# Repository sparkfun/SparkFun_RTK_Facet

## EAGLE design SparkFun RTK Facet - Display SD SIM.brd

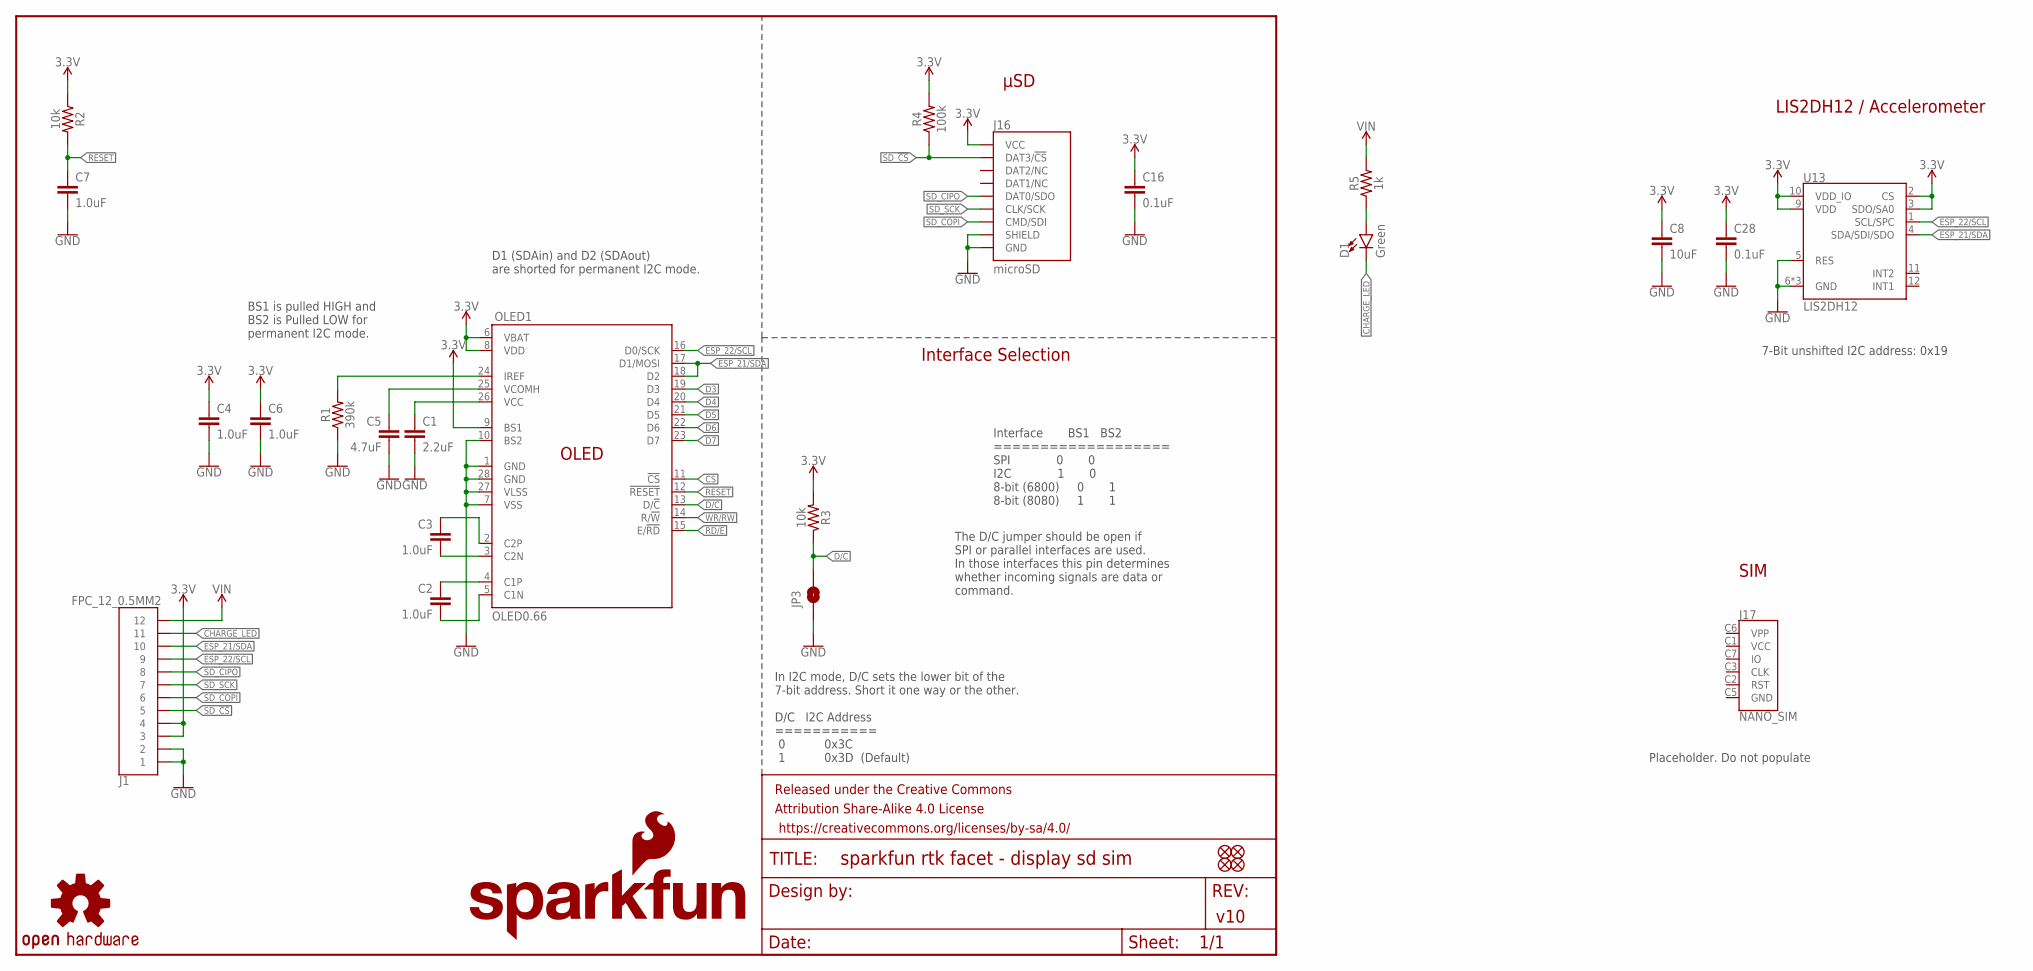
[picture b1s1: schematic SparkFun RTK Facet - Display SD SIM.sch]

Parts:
C1: 2.2uF; 0805
C2, C3: 1.0uF; 0805
C4, C6, C7: 1.0uF; 0603
C5: 4.7uF; 1206
C8: 10uF; 0603
C16, C28: 0.1uF; 0603
D1: Green; LED-1206-BOTTOM
FID1, FID2, FID3, FID4: FIDUCIAL1X2; FIDUCIAL-1X2
FRAME1: FRAME-LETTER; CREATIVE_COMMONS
J1: FPC_12_0.5MM2; FPC_12_FLIP_DOUBLESIDED_2
J16: microSD; MICRO-SD-SOCKET
J17: NANO_SIM; NANO_SIM_WURTH_693043020611
JP3: JUMPER-SMT_2_NO_SILK; SMT-JUMPER_2_NO_SILK
LOGO3: OSHW-LOGOS; OSHW-LOGO-S
LOGO5: SFE_LOGO_NAME_FLAME.1_INCH; SFE_LOGO_NAME_FLAME_.1
OLED1: OLED0.66; OLED-0.66-64X48
R1: 390k; 0603
R2, R3: 10k; 0603
R4: 100k; 0603
R5: 1k; 0603
U13: LIS2DH12; LGA-12-LISDH12

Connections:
3.3V: C4.1, C6.1, C8.1, C16.1, C28.1, J1.3, J1.4, J16.VCC, OLED1.6 (VBAT), OLED1.8 (VDD), OLED1.9 (BS1), R2.1, R3.2, R4.2, U13.2 (CS), U13.3 (SDO/SA0), U13.9 (VDD), U13.10 (VDD_IO)
C1P: C2.1, OLED1.4 (C1P)
C2N: C3.2, OLED1.3 (C2N)
CHARGE_LED: D1.C, J1.11
CS: OLED1.11 (!CS!)
D3: OLED1.19 (D3)
D4: OLED1.20 (D4)
D5: OLED1.21 (D5)
D6: OLED1.22 (D6)
D7: OLED1.23 (D7)
D/C: JP3.2, OLED1.13 (D/!C!), R3.1
ESP_21/SDA: J1.10, OLED1.17 (D1/MOSI), OLED1.18 (D2), U13.4 (SDA/SDI/SDO)
ESP_22/SCL: J1.9, OLED1.16 (D0/SCK), U13.1 (SCL/SPC)
GND: C1.2, C4.2, C5.2, C6.2, C7.2, C8.2, C16.2, C28.2, J1.1, J1.2, J16.CD1 (SHIELD), J16.GND, J16.GND1 (GND), J16.GND3 (GND), JP3.1, OLED1.1 (GND), OLED1.7 (VSS), OLED1.10 (BS2), OLED1.27 (VLSS), OLED1.28 (GND), R1.1, U13.5 (RES), U13.6 (GND), U13.7 (GND), U13.8 (GND)
IREF: OLED1.24 (IREF), R1.2
unnamed: C3.1, OLED1.2 (C2P)
unnamed: C2.2, OLED1.5 (C1N)
unnamed: D1.A, R5.1
RD/E: OLED1.15 (E/!RD!)
RESET: C7.1, OLED1.12 (!RESET!), R2.2
SD_!CS!: J1.5, J16.CS/DAT3 (DAT3/!CS!), R4.1
SD_CIPO: J1.8, J16.DO/DAT0 (DAT0/SDO)
SD_COPI: J1.6, J16.DI/CMD (CMD/SDI)
SD_SCK: J1.7, J16.SCLK (CLK/SCK)
VCC: C1.1, OLED1.26 (VCC)
VCOMH: C5.1, OLED1.25 (VCOMH)
VIN: J1.12, R5.2
WR/RW: OLED1.14 (R/!W!)

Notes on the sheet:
v10
Interface BS1 BS2 =================== SPI 0 0 I2C 1 0 8-bit (6800) 0 1 8-bit (8080) 1 1
Interface Selection
D1 (SDAin) and D2 (SDAout) are shorted for permanent I2C mode.
In I2C mode, D/C sets the lower bit of the 7-bit address. Short it one way or the other. D/C I2C Address =========== 0 0x3C 1 0x3D (Default)
The D/C jumper should be open if SPI or parallel interfaces are used. In those interfaces this pin determines whether incoming signals are data or command.
BS1 is pulled HIGH and BS2 is Pulled LOW for permanent I2C mode.
μSD
7-Bit unshifted I2C address: 0x19
LIS2DH12 / Accelerometer
SIM
Placeholder. Do not populate

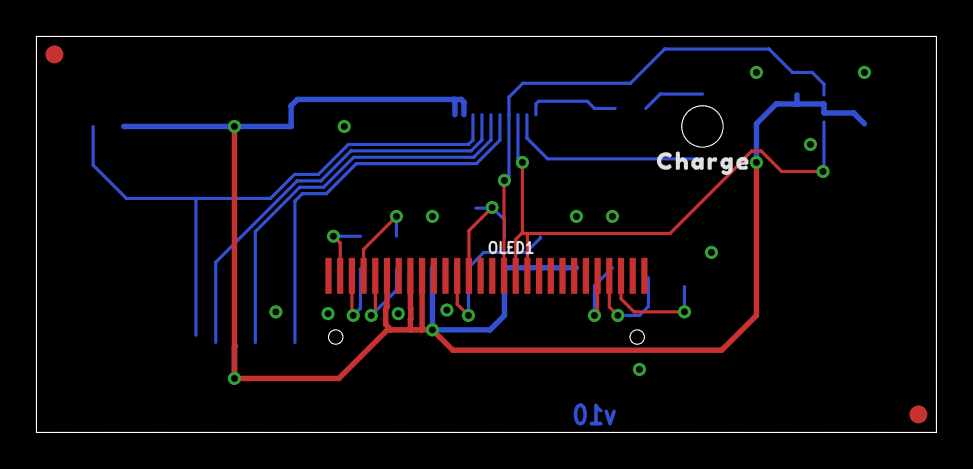
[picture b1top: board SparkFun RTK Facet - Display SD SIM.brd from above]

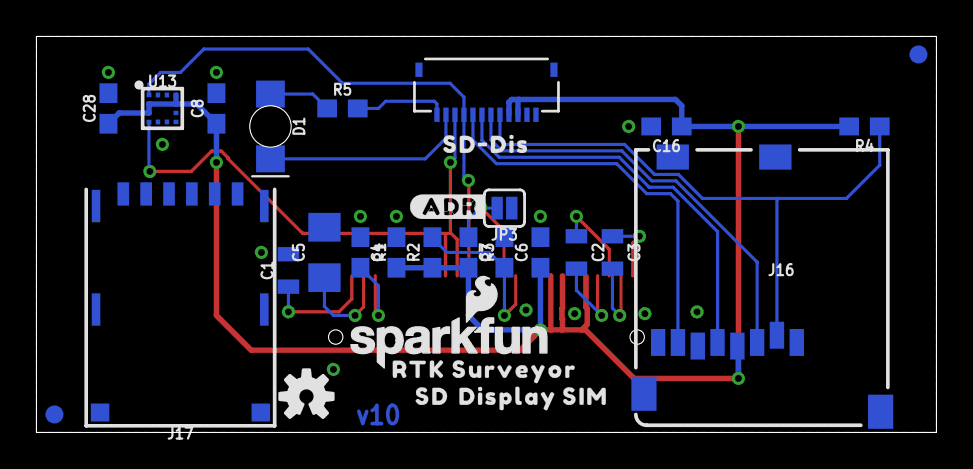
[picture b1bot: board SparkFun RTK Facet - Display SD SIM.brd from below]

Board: 2 copper layers, 50.0 x 22.0 mm, 36 parts (31 on the bottom side), 20 nets.

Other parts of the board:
U$1: SD#DIS0
U$3: DISPLAY0
U$4: SD1
U$5: SIM2
U$6: RTK_SURVEYOR0
U$7: #ADR#0
U$8: CHARGE0

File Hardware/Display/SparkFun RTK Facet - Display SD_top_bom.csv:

Comment,Designator,Footprint,LCSC Part #
OLED0.66-TRIMTRIM,OLED1,OLED-0.66-64X48-TRIM,C88334 
0.1uF,C16 C28,603,C1590 
1.0uF,C2 C3,805,C15849 
1.0uF,C4 C6 C7,603,C1592 
1k,R5,603,C22548 
2.2uF,C1,805,C19110 
4.7uF,C5,1206,C51205 
10k,R2 R3,603,C98220 
10uF,C8,603,C19702 
100k,R4,603,C14675 
390k,R1,603,C863775 
FPC_12_0.5MM_BACKFLIP,J1,FPC_12_DOUBLESIDED_BACKFLIP,C5213751 
Green,D1,LED-1206-BOTTOM,C125106 
MICRO-SD-PUSH-PUSH-EXT-PIN,J2,MICROSD-EXTERNALPIN,C720505 
MOMENTARY-SWITCH-SPST-SMD-5.2MM-TALL,S1,TACTILE_SWITCH_SMD_5.2MM,C318887 
6P_1MM-LIF Connector,JP1,6P_1MM-LIF Connector,C2915488

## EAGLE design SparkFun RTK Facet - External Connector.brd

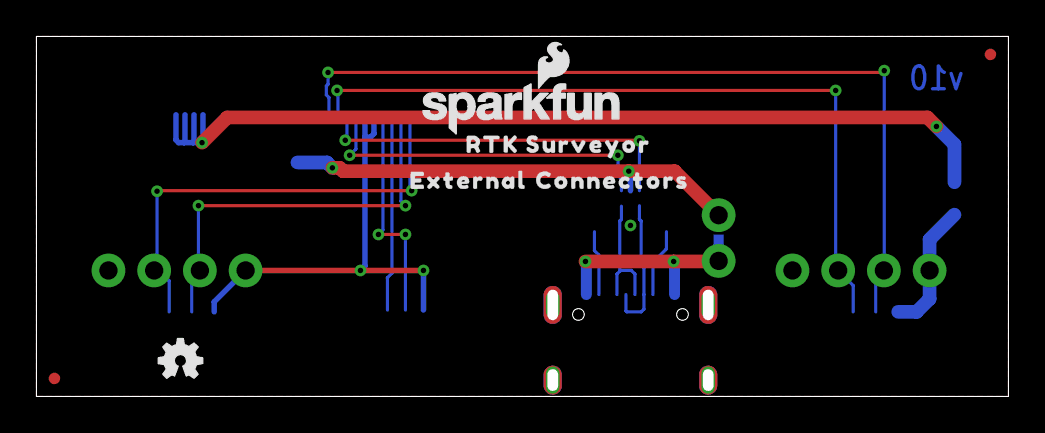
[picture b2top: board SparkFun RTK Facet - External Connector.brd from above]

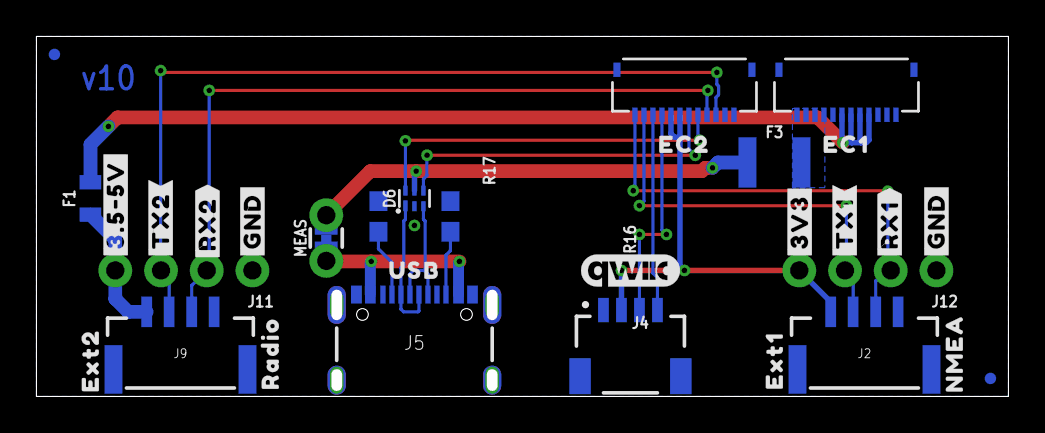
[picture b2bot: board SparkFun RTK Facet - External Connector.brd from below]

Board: 2 copper layers, 54.0 x 20.0 mm, 40 parts (33 on the bottom side), 19 nets.

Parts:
D6: PRTR5V0U2F; SOT886
F1: 6V 0.5A; 0805
F3: 6V/2A; 1210
FRAME1: FRAME-LETTER; CREATIVE_COMMONS
J1, J6: FPC_12_0.5MM2; FPC_12_FLIP_DOUBLESIDED_2
J2, J9: JST-4-SMD-1.25MM-LOCKING
J4: Qwiic; JST04_1MM_RA
J5: u-blox USB; USB-C-16P-2LAYER-PADS
J11, J12: 1X04_NO_SILK
JP21, JP61, JP71, JP81: FIDUCIALUFIDUCIAL; FIDUCIAL-MICRO
LOGO1: OSHW-LOGOMINI; OSHW-LOGO-MINI
LOGO2: SFE_LOGO_NAME_FLAME.1_INCH; SFE_LOGO_NAME_FLAME_.1
LOGO3: QWIIC_LOGO_CONNECTOR; QWIIC_5.5MM
MEAS: COMBO-JUMPER_2_NC_TRACE
R16, R17: 5.1k; 0603
U$1: USB0
U$2: CONNECTORS1
U$4: EXT10
U$5: #3V3#0
U$6: EXT22
U$7: NMEA1
U$8: EC10
U$9: EXTERNAL0
U$10: RTK_SURVEYOR0
U$11: EC21
U$12: RADIO3
U$23: #3#5#5V#0
U$38, U$82: #GND#0
U$39: #RX2#2
U$40: #TX2#1
U$65: #TX1#1
U$68: #RX1#2

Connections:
3.3V: J2.1, J4.2, J6.7, J6.8, J12.4
CC1: J5.A5, R17.2
CC2: J5.B5, R16.2
ESP_21/SDA: J4.3, J6.9
ESP_22/SCL: J4.4, J6.10
EXTERNAL_SERIAL1_RXI: J2.3, J6.12, J12.2
EXTERNAL_SERIAL1_TXO: J2.2, J6.11, J12.3
GND: D6.2, J1.1, J1.2, J1.3, J2.4, J4.1, J5.GND, J5.GND2, J5.SHLD1, J5.SHLD2, J5.SHLD3, J5.SHLD4, J6.1, J6.2, J9.4, J11.1, J12.1, R16.1, R17.1
unnamed: F1.1, J9.1, J11.4
USB1_D_M: D6.1, J5.A7, J5.B7
USB1_D_P: D6.3, J5.A6, J5.B6
USB_DM: D6.6, J6.5
USB_DP: D6.4, J6.6
VIN: J5.VBUS1, J5.VBUS2, MEAS.1, MEAS.3
VIN1: D6.5, F3.1, MEAS.2, MEAS.4
V_BATT: F1.2, J1.4, J1.5, J1.6, J1.7
V_USB: F3.2, J1.9, J1.10, J1.11, J1.12
ZED-RXI2: J6.4, J9.3, J11.2
ZED-TXO2: J6.3, J9.2, J11.3

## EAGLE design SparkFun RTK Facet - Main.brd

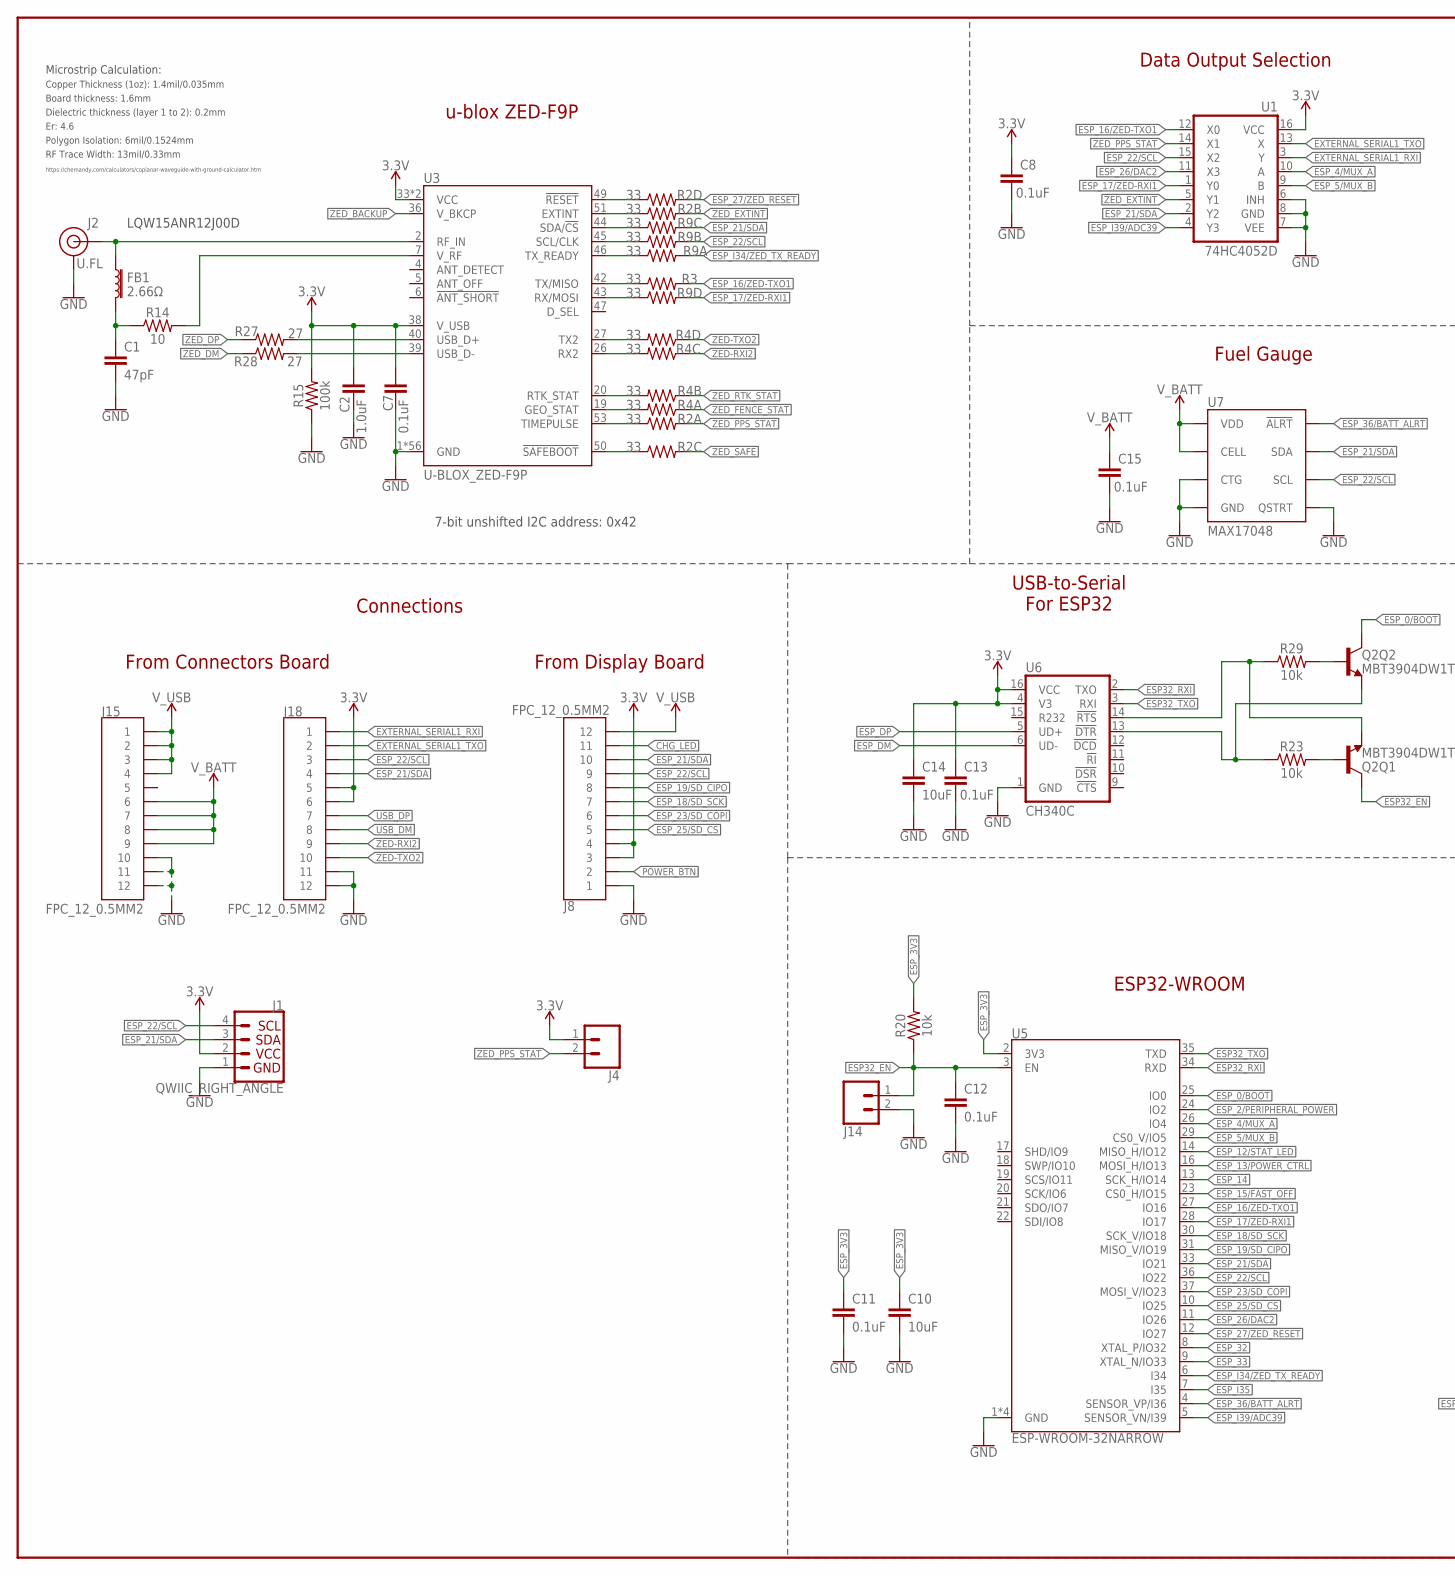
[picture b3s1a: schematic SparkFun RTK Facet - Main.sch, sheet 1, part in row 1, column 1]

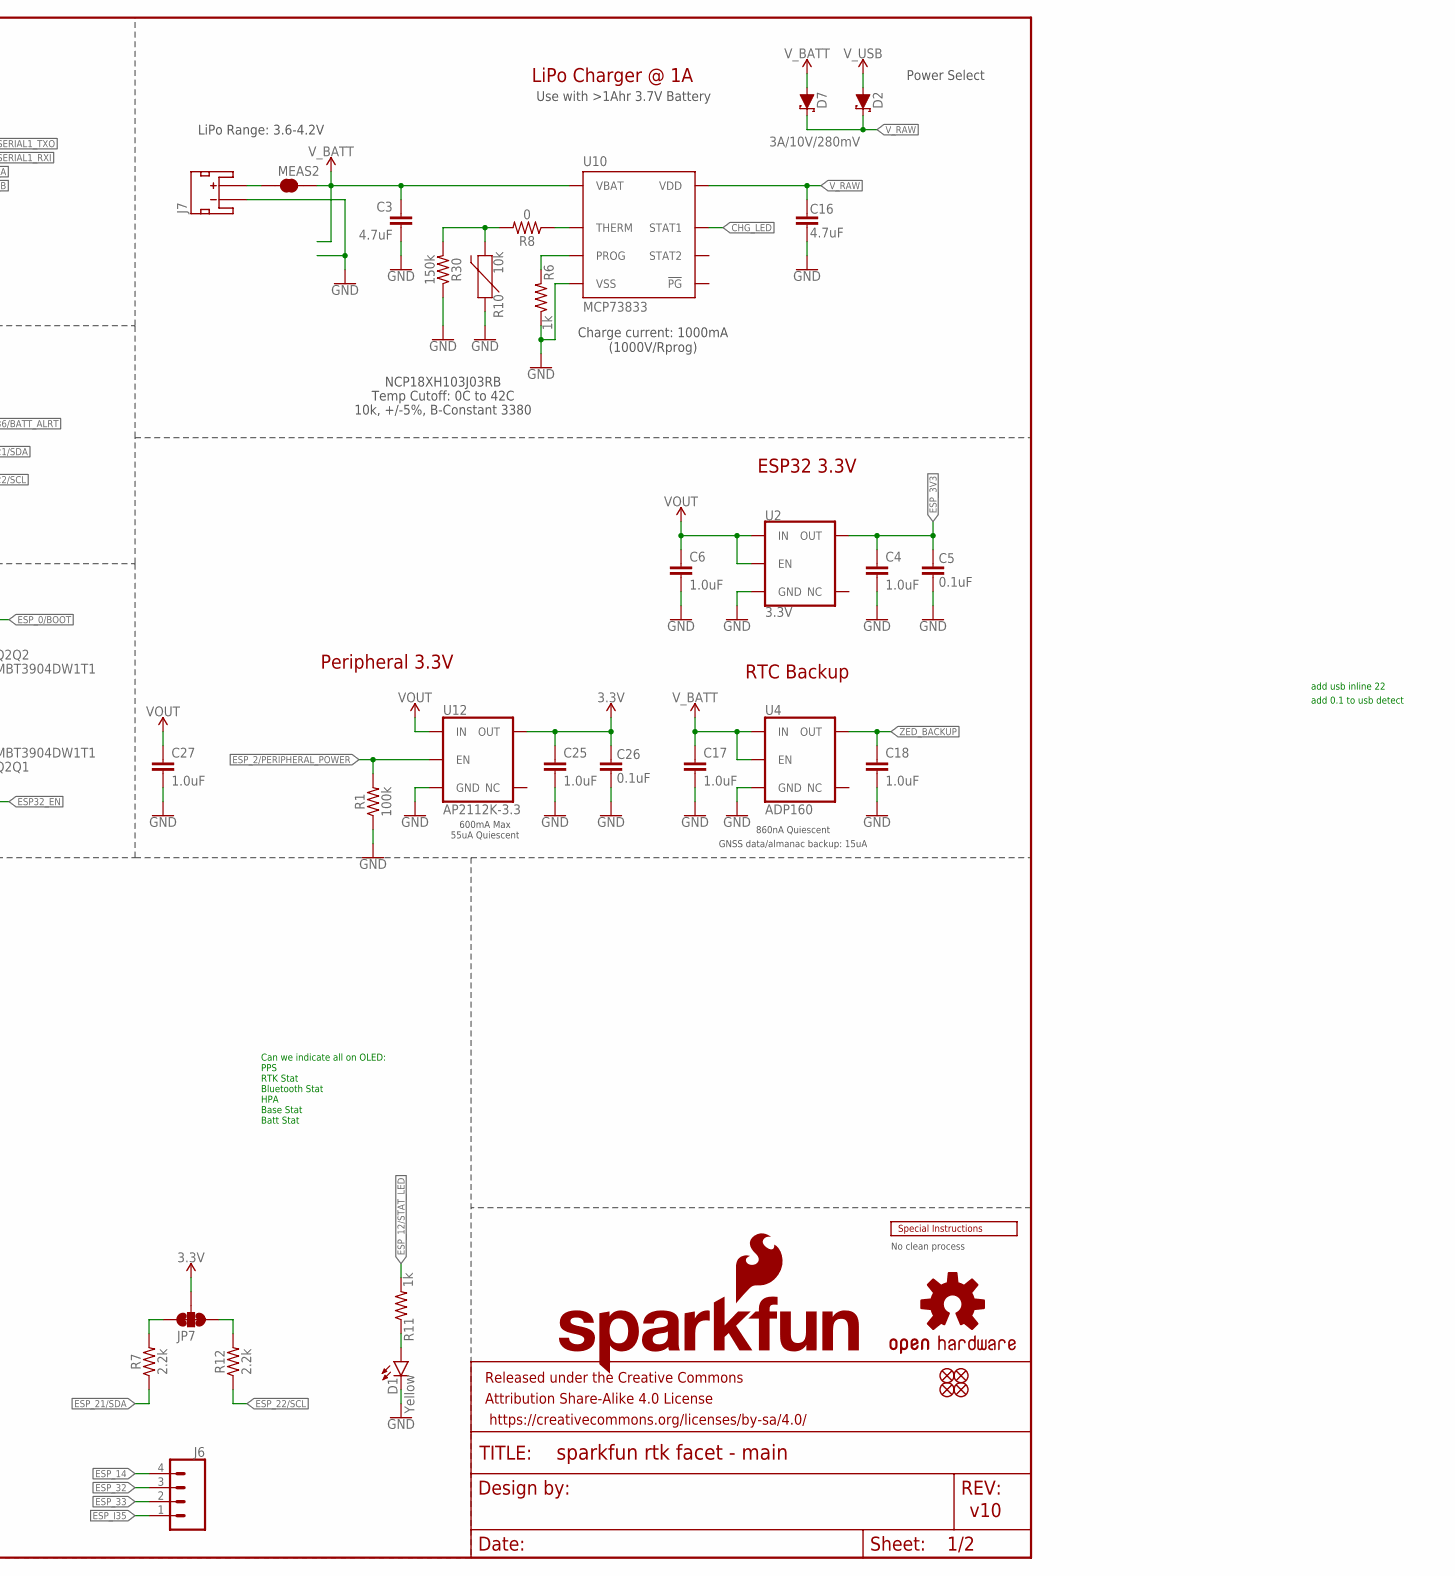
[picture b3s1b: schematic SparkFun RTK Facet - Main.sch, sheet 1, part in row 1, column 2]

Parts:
C1: 47pF; 0402
C2, C4, C6, C17, C18, C25, C27: 1.0uF; 0603
C3, C16: 4.7uF; 0603
C5, C7, C8, C11, C12, C13, C15, C26: 0.1uF; 0603
C10, C14: 10uF; 0603
D1: Yellow; LED-0603
D2, D7: 3A/10V/280mV; SOD-323
FB1: 2.66Ω; 0402-TIGHT
FRAME2: FRAME-LEDGER; CREATIVE_COMMONS
J1: QWIIC_RIGHT_ANGLE; JST04_1MM_RA
J2: U.FL
J4, J14: CONN_021X02_NO_SILK; 1X02_NO_SILK
J6: CONN_041X04_NO_SILK_NO_POP; 1X04_NO_SILK
J7: JST_2MM_MALE; JST-2-SMD
J8, J15, J18: FPC_12_0.5MM2; FPC_12_FLIP_DOUBLESIDED_2
JP7: JUMPER-SMT_3_2-NC_TRACE_SILK; SMT-JUMPER_3_2-NC_TRACE_SILK
JP21, JP61, JP71, JP81: FIDUCIALUFIDUCIAL; FIDUCIAL-MICRO
LOGO1: OSHW-LOGOMINI; OSHW-LOGO-MINI
LOGO2: SFE_LOGO_NAME_FLAME.1_INCH; SFE_LOGO_NAME_FLAME_.1
MEAS2: JUMPER-COMBO_2_NC_TRACE; COMBO-JUMPER_2_NC_TRACE
Q2: MBT3904DW1T1; SC70-6
R1, R15: 100k; 0603
R2, R4, R9: 33; 1206_RA
R3: 33; 0603
R6, R11: 1k; 0603
R7, R12: 2.2k; 0603
R8: 0; 0603
R10, R20, R23, R29: 10k; 0603
R14: 10; 0603
R27, R28: 27; 0603
R30: 150k; 0603
U1: 74HC4052D; SO16
U2: 3.3V; SOT23-5
U3: U-BLOX_ZED-F9P; ZED-F9P
U4: ADP160; SOT23-5
U5: ESP-WROOM-32NARROW; ESP-WROOM-32-NARROW
U6: CH340C; SO016
U7: MAX17048; DFN-8
U10: MCP73833; DFN-10
U12: AP2112K-3.3; SOT23-5
U$2: SPECIAL_INSTRUCTIONS-ORDERING; ORDERING_INSTRUCTIONS

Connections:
3.3V: C2.1, C7.2, C8.1, C13.1, C14.1, C25.1, C26.2, J1.2, J4.1, J8.3, J8.4, J18.5, J18.6, JP7.2, R15.2, U1.16 (VCC), U3.33 (VCC), U3.34 (VCC), U3.38 (V_USB), U6.4 (V3), U6.16 (VCC), U12.5 (OUT); also elsewhere on the board
ANT_VCC: C1.1, FB1.2, R14.1
CHG_LED: J8.11, U10.3 (STAT1)
CHG_THERM1: R8.2, R10.2, R30.2
ESP32_!DTR: Q2.1 (E), R23.1, U6.13 (!DTR)
ESP32_!RTS: Q2.4 (E), R29.1, U6.14 (!RTS)
ESP32_EN: C12.1, J14.1, Q2.3 (C), R20.1, U5.3 (EN)
ESP32_RXI: U5.34 (RXD), U6.2 (TXO)
ESP32_TXO: U5.35 (TXD), U6.3 (RXI)
ESP_0/BOOT: Q2.6 (C), U5.25 (IO0)
ESP_2/PERIPHERAL_POWER: R1.2, U5.24 (IO2), U12.3 (EN)
ESP_3V3: C4.1, C5.2, C10.1, C11.1, R20.2, U2.5 (OUT), U5.2 (3V3)
ESP_4/MUX_A: U1.10 (A), U5.26 (IO4)
ESP_5/MUX_B: U1.9 (B), U5.29 (CS0_V/IO5)
ESP_12/STAT_LED: R11.2, U5.14 (MISO_H/IO12)
ESP_13/POWER_CTRL: U5.16 (MOSI_H/IO13); also elsewhere on the board
ESP_14: J6.4, U5.13 (SCK_H/IO14)
ESP_15/FAST_OFF: U5.23 (CS0_H/IO15); also elsewhere on the board
ESP_16/ZED-TXO1: R3.2, U1.12 (X0), U5.27 (IO16)
ESP_17/ZED-RXI1: R9.P5 (2), U1.1 (Y0), U5.28 (IO17)
ESP_18/SD_SCK: J8.7, U5.30 (SCK_V/IO18)
ESP_19/SD_CIPO: J8.8, U5.31 (MISO_V/IO19)
ESP_21/SDA: J1.3, J8.10, J18.4, R7.1, R9.P6 (2), U1.2 (Y2), U5.33 (IO21), U7.8 (SDA); also elsewhere on the board
ESP_22/SCL: J1.4, J8.9, J18.3, R9.P7 (2), R12.1, U1.15 (X2), U5.36 (IO22), U7.7 (SCL); also elsewhere on the board
ESP_23/SD_COPI: J8.6, U5.37 (MOSI_V/IO23)
ESP_25/SD_!CS!: J8.5, U5.10 (IO25)
ESP_26/DAC2: U1.11 (X3), U5.11 (IO26)
ESP_27/ZED_!RESET!: R2.P5 (2), U5.12 (IO27)
ESP_32: J6.3, U5.8 (XTAL_P/IO32)
ESP_33: J6.2, U5.9 (XTAL_N/IO33)
ESP_36/BATT_ALRT: U5.4 (SENSOR_VP/I36), U7.5 (!ALRT)
ESP_DM: U6.6 (UD-); also elsewhere on the board
ESP_DP: U6.5 (UD+); also elsewhere on the board
ESP_I34/ZED_TX_READY: R9.P8 (2), U5.6 (I34)
ESP_I35: J6.1, U5.7 (I35)
ESP_I39/ADC39: U1.4 (Y3), U5.5 (SENSOR_VN/I39)
EXTERNAL_SERIAL1_RXI: J18.1, U1.3 (Y)
EXTERNAL_SERIAL1_TXO: J18.2, U1.13 (X)
FENCE_LV: R4.P8 (2), U3.19 (GEO_STAT)
GND: C1.2, C2.2, C3.2, C4.2, C5.1, C6.2, C7.1, C8.2, C10.2, C11.2, C12.2, C13.2, C14.2, C15.2, C16.2, C17.2, C18.2, C25.2, C26.1, C27.2, D1.C, J1.1, J2.1 (GND), J2.2 (GND), J7.1 (-), J8.1, J14.2, J15.10, J15.11, J15.12, J18.11, J18.12, R1.1, R6.1, R10.1, R15.1, R30.1, U1.6 (INH), U1.7 (VEE), U1.8 (GND), U2.2 (GND), U3.1 (GND), U3.3 (GND), U3.12 (GND), U3.14 (GND), U3.32 (GND), U3.37 (GND), U3.41 (GND), U3.48 (GND), U3.55 (GND), U3.56 (GND), U3.57 (GND), U3.58 (GND), U3.59 (GND), U3.60 (GND), U3.61 (GND), U3.62 (GND), U3.63 (GND), U3.64 (GND), U3.65 (GND), U3.66 (GND), U3.67 (GND), U3.68 (GND), U3.69 (GND), U3.70 (GND), U3.71 (GND), U3.72 (GND), U3.73 (GND), U3.74 (GND), U3.75 (GND), U3.76 (GND), U3.77 (GND), U3.78 (GND), U3.79 (GND), U3.80 (GND), U3.81 (GND), U3.82 (GND), U3.83 (GND), U3.84 (GND), U3.85 (GND), U3.86 (GND), U3.87 (GND), U3.88 (GND), U3.89 (GND), U3.90 (GND), U3.91 (GND), U3.92 (GND), U3.93 (GND), U3.94 (GND), U3.95 (GND), U3.96 (GND), U3.97 (GND), U3.98 (GND), U3.99 (GND), U3.100 (GND), U3.101 (GND), U3.102 (GND), U4.2 (GND), U5.1 (GND), U5.15 (GND), U5.38 (GND), U5.GND, U6.1 (GND), U7.1 (CTG), U7.4 (GND), U7.6 (QSTRT), U7.9 (GND), U10.5 (VSS), U10.11 (VSS), U12.2 (GND); also elsewhere on the board
GPS_ANT1: FB1.1, J2.FEED (SIGNAL), U3.2 (RF_IN)
LIPO_RAW: J7.2 (+), MEAS2.1, MEAS2.3 (1)
unnamed: R8.1, U10.8 (THERM)
unnamed: D1.A, R11.1
unnamed: JP7.3, R7.2
unnamed: JP7.1, R12.2
unnamed: R2.P2 (1), U3.51 (EXTINT)
unnamed: R27.2, U3.40 (USB_D+)
unnamed: R28.2, U3.39 (USB_D-)
unnamed: R14.2, U3.7 (V_RF)
unnamed: R2.P4 (1), U3.49 (!RESET!)
unnamed: R2.P3 (1), U3.50 (!SAFEBOOT!)
unnamed: R9.P1 (1), U3.46 (TX_READY)
unnamed: Q2.5 (B), R23.2
unnamed: Q2.2 (B), R29.2
POWER_BTN: J8.2; also elsewhere on the board
PPS: R2.P1 (1), U3.53 (TIMEPULSE)
PROG1: R6.2, U10.6 (PROG)
RTK_LV: R4.P7 (2), U3.20 (RTK_STAT)
RX2_LV: R4.P6 (2), U3.26 (RX2)
RXLV: R9.P4 (1), U3.43 (RX/MOSI)
SCL_LV: R9.P2 (1), U3.45 (SCL/CLK)
SDA_LV: R9.P3 (1), U3.44 (SDA/!CS!)
TX2_LV: R4.P5 (2), U3.27 (TX2)
TXLV: R3.1, U3.42 (TX/MISO)
USB_DM: J18.8; also elsewhere on the board
USB_DP: J18.7; also elsewhere on the board
VOUT: C6.1, C27.1, U2.1 (IN), U2.3 (EN), U12.1 (IN); also elsewhere on the board
V_BATT: C3.1, C15.1, C17.1, D7.A, J15.6, J15.7, J15.8, J15.9, MEAS2.2, MEAS2.4 (2), U4.1 (IN), U4.3 (EN), U7.2 (CELL), U7.3 (VDD), U10.9 (VBAT), U10.10 (VBAT)
V_RAW: C16.1, D2.C, D7.C, U10.1 (VDD), U10.2 (VDD); also elsewhere on the board
V_USB: D2.A, J8.12, J15.1, J15.2, J15.3, J15.4; also elsewhere on the board
ZED-RXI2: J18.9, R4.P3 (1)
ZED-TXO2: J18.10, R4.P4 (1)
ZED_!SAFE!: R2.P6 (2)
ZED_BACKUP: C18.1, U3.36 (V_BKCP), U4.5 (OUT)
ZED_DM: R28.1; also elsewhere on the board
ZED_DP: R27.1; also elsewhere on the board
ZED_EXTINT: R2.P7 (2), U1.5 (Y1)
ZED_FENCE_STAT: R4.P1 (1)
ZED_PPS_STAT: J4.2, R2.P8 (2), U1.14 (X1)
ZED_RTK_STAT: R4.P2 (1)

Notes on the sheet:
v10
7-bit unshifted I2C address: 0x42
u-blox ZED-F9P
RTC Backup
LQW15ANR12J00D
Board thickness: 1.6mm
Er: 4.6
Copper Thickness (1oz): 1.4mil/0.035mm
RF Trace Width: 13mil/0.33mm
Polygon Isolation: 6mil/0.1524mm
No clean process
Dielectric thickness (layer 1 to 2): 0.2mm
https://chemandy.com/calculators/coplanar-waveguide-with-ground-calculator.htm
Microstrip Calculation:
Connections
ESP32 3.3V
ESP32-WROOM
USB-to-Serial For ESP32
Data Output Selection
Fuel Gauge
Can we indicate all on OLED: PPS RTK Stat Bluetooth Stat HPA Base Stat Batt Stat
From Connectors Board
From Display Board
LiPo Range: 3.6-4.2V
Charge current: 1000mA (1000V/Rprog)
Use with >1Ahr 3.7V Battery
LiPo Charger @ 1A
NCP18XH103J03RB
10k, +/-5%, B-Constant 3380
Temp Cutoff: 0C to 42C
Power Select
860nA Quiescent
GNSS data/almanac backup: 15uA
Peripheral 3.3V
600mA Max 55uA Quiescent
add usb inline 22
add 0.1 to usb detect

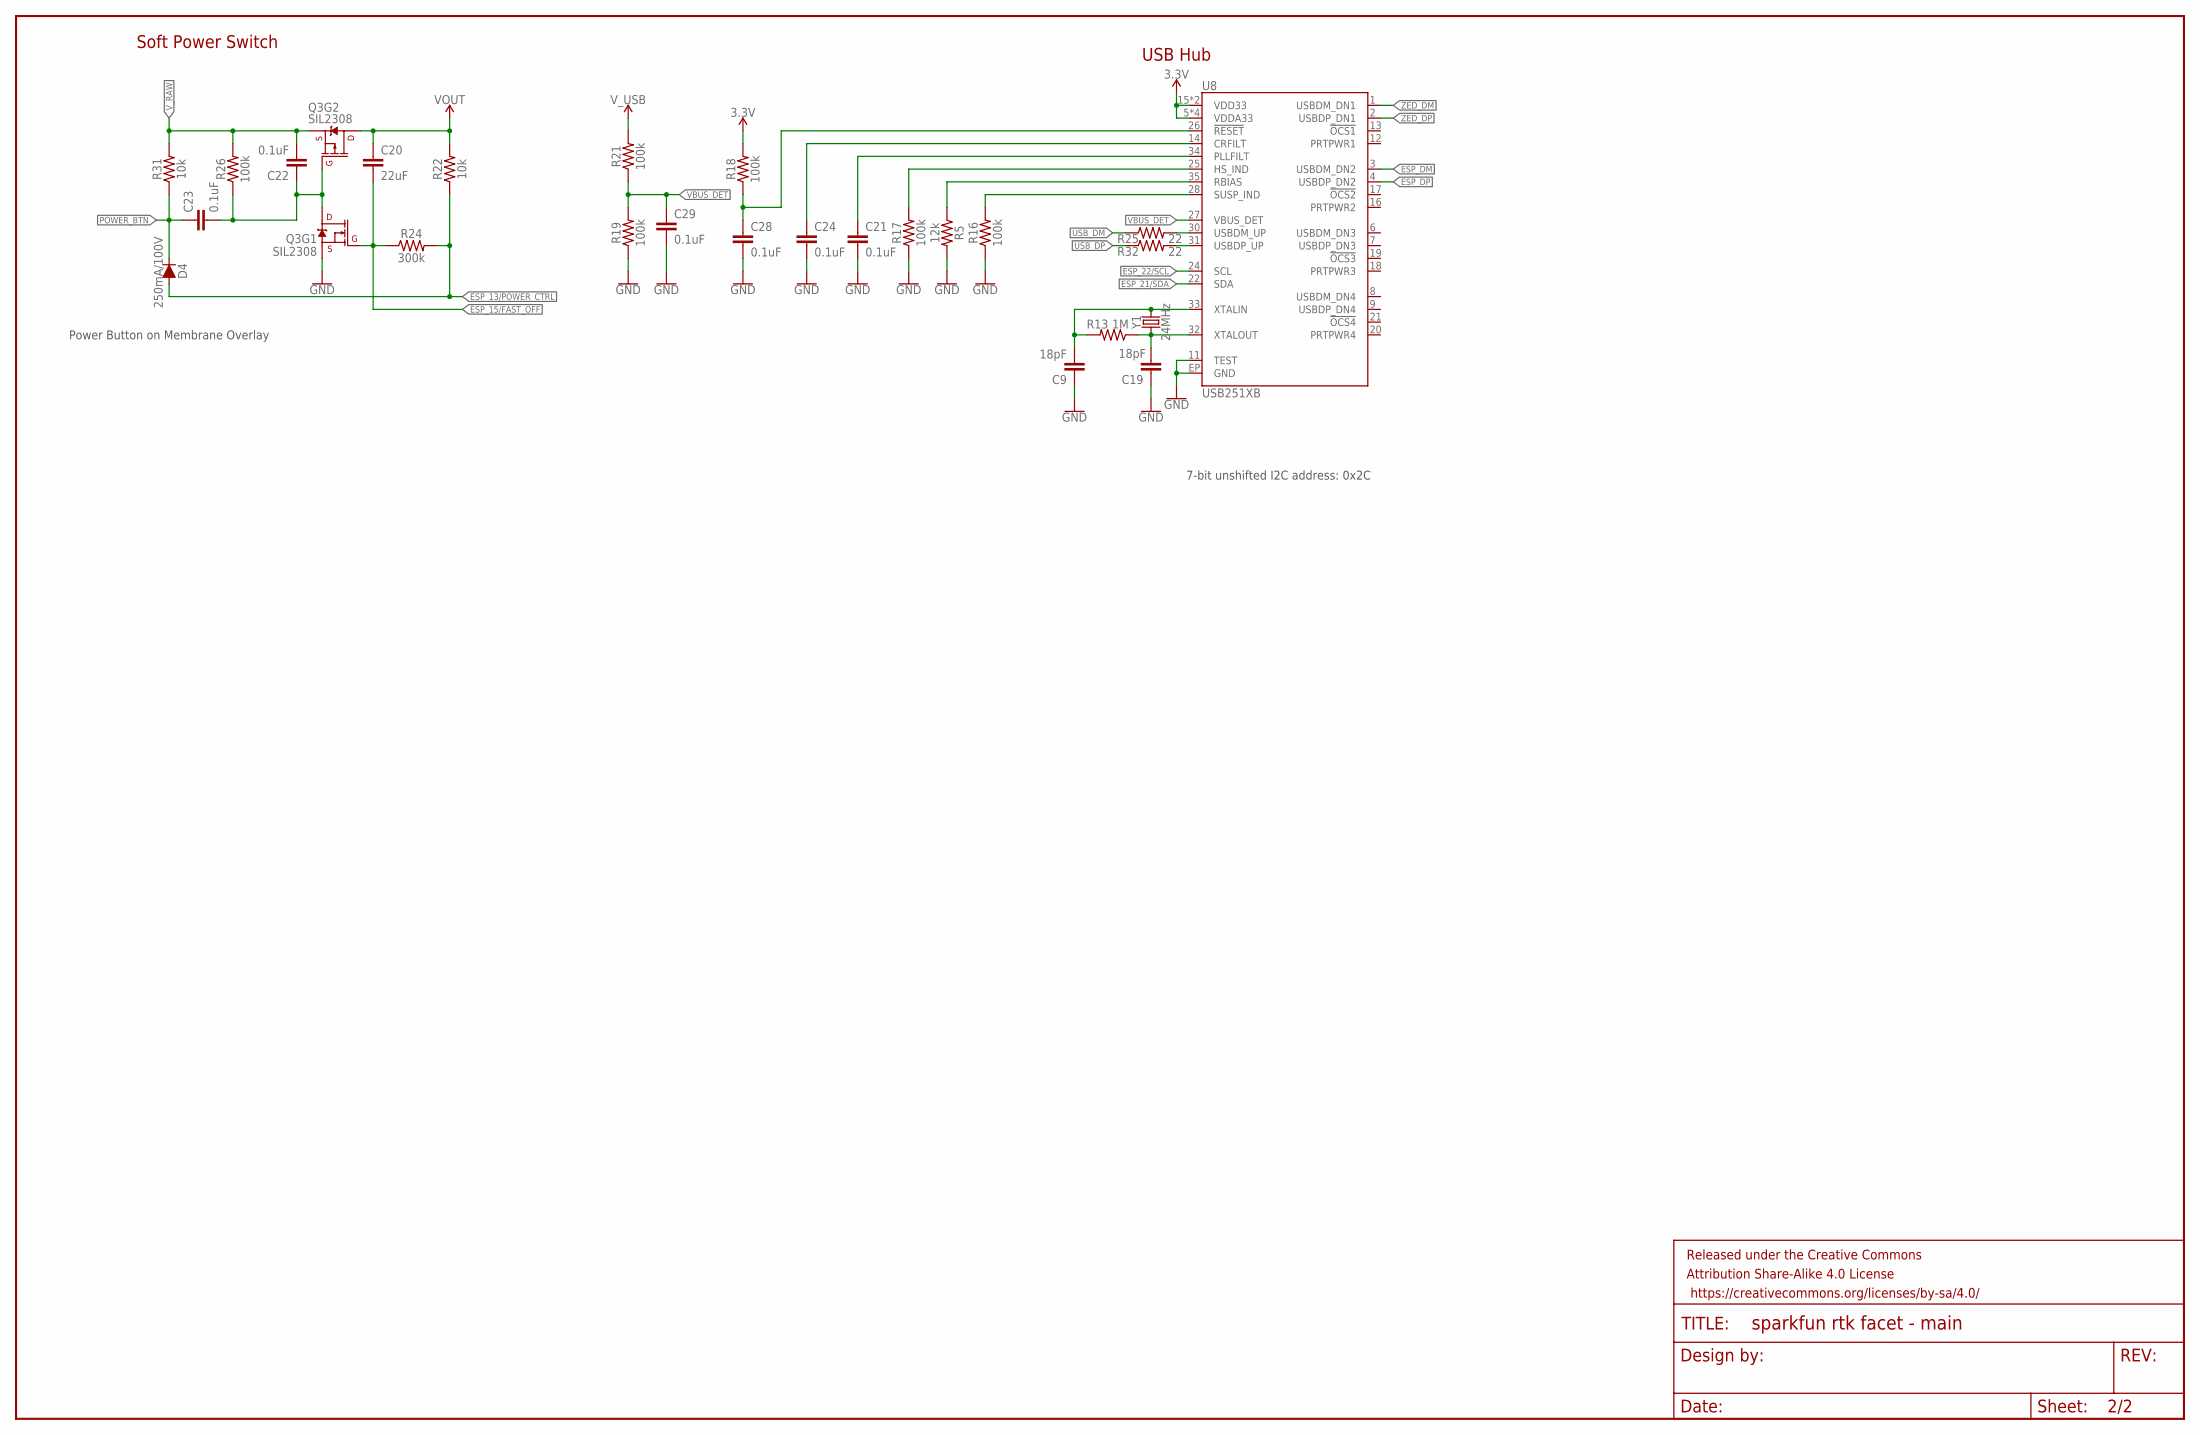
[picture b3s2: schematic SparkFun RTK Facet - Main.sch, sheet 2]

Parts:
C9, C19: 18pF; 0603
C20: 22uF; 0603
C21, C22, C23, C24, C28, C29: 0.1uF; 0603
D4: 250mA/100V; SOD-323
FRAME1: FRAME-LEDGER; CREATIVE_COMMONS
Q3: SIL2308; SOT26
R5: 12k; 0603
R13: 1M; 0603
R16, R17, R18, R19, R21, R26: 100k; 0603
R22, R31: 10k; 0603
R24: 300k; 0603
R25, R32: 22; 0603
U8: USB251XB; QFN-36
Y1: 24MHz; CRYSTAL-SMD-2.0X1.6MM

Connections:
3.3V: R18.2, U8.5 (VDDA33), U8.10 (VDDA33), U8.15 (VDD33), U8.23 (VDD33), U8.29 (VDDA33), U8.36 (VDDA33); also elsewhere on the board
ESP_13/POWER_CTRL: D4.A, R22.1, R24.2; also elsewhere on the board
ESP_15/FAST_OFF: C20.2, Q3.G1 (G), R24.1; also elsewhere on the board
ESP_21/SDA: U8.22 (SDA); also elsewhere on the board
ESP_22/SCL: U8.24 (SCL); also elsewhere on the board
ESP_DM: U8.3 (USBDM_DN2); also elsewhere on the board
ESP_DP: U8.4 (USBDP_DN2); also elsewhere on the board
GND: C9.1, C19.1, C21.2, C24.2, C28.2, C29.2, Q3.S1 (S), R5.2, R16.1, R17.1, R19.1, U8.11 (TEST), U8.EP (GND); also elsewhere on the board
unnamed: C22.1, C23.2, Q3.D1 (D), Q3.G2 (G), R26.1
unnamed: C9.2, R13.2, U8.33 (XTALIN), Y1.3 (2)
unnamed: C19.2, R13.1, U8.32 (XTALOUT), Y1.1
unnamed: R5.1, U8.35 (RBIAS)
unnamed: R16.2, U8.28 (SUSP_IND)
unnamed: R17.2, U8.25 (HS_IND)
unnamed: C21.1, U8.34 (PLLFILT)
unnamed: C24.1, U8.14 (CRFILT)
unnamed: R25.2, U8.30 (USBDM_UP)
unnamed: R32.2, U8.31 (USBDP_UP)
POWER_BTN: C23.1, D4.C, R31.1; also elsewhere on the board
USB_!RESET: C28.1, R18.1, U8.26 (!RESET)
USB_DM: R25.1; also elsewhere on the board
USB_DP: R32.1; also elsewhere on the board
VBUS_DET: C29.1, R19.2, R21.1, U8.27 (VBUS_DET)
VOUT: C20.1, Q3.D2 (D), R22.2; also elsewhere on the board
V_RAW: C22.2, Q3.S2 (S), R26.2, R31.2; also elsewhere on the board
V_USB: R21.2; also elsewhere on the board
ZED_DM: U8.1 (USBDM_DN1); also elsewhere on the board
ZED_DP: U8.2 (USBDP_DN1); also elsewhere on the board

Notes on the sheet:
Soft Power Switch
7-bit unshifted I2C address: 0x2C
USB Hub
Power Button on Membrane Overlay

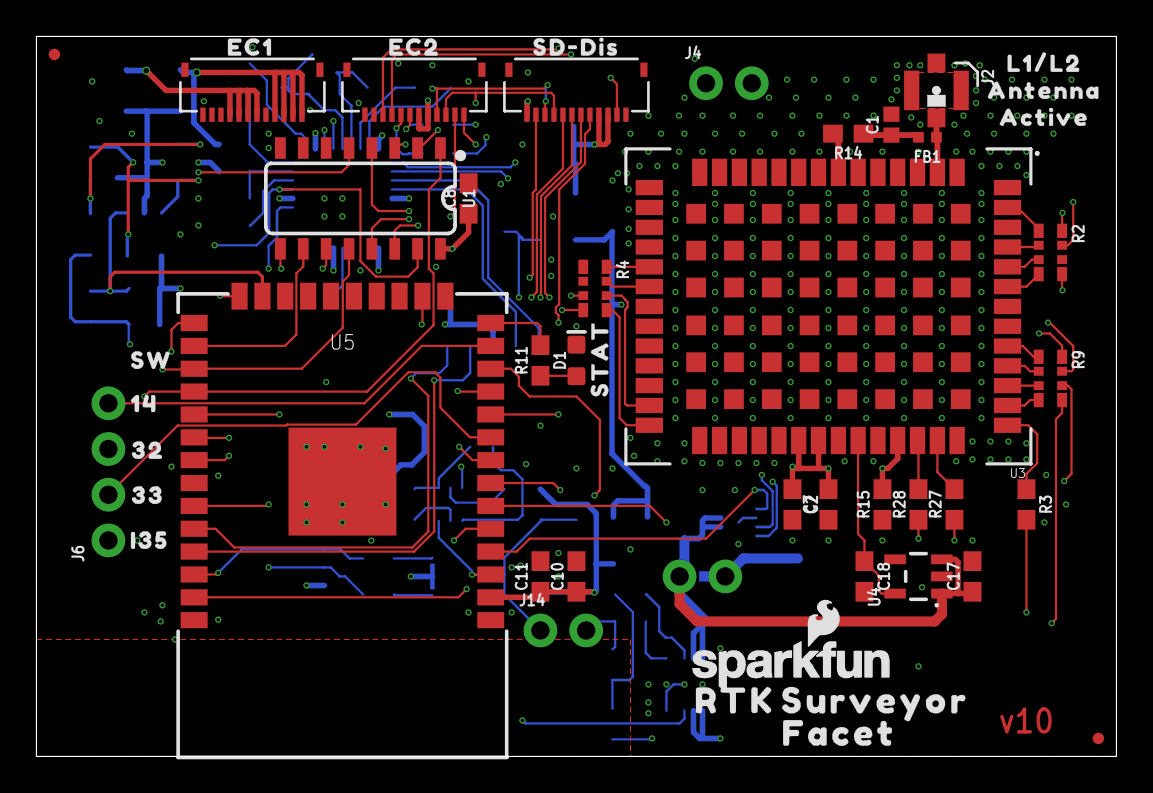
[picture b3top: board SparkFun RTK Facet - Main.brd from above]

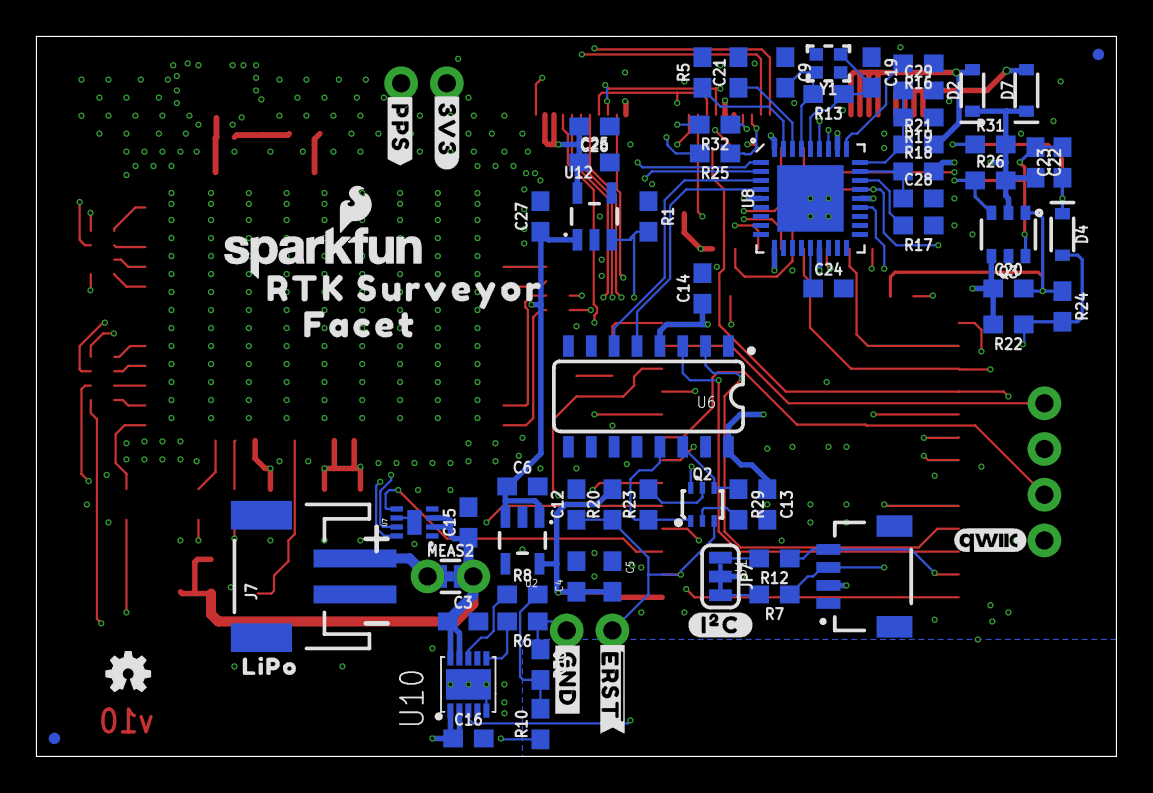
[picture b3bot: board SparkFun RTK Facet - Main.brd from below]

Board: 4 copper layers, 60.0 x 40.0 mm, 125 parts (74 on the bottom side), 90 nets.

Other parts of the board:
LOGO3: SFE_LOGO_NAME_FLAME.1_INCH; SFE_LOGO_NAME_FLAME_.1
U$1: LIPO0
U$3: EC21
U$4: SD#DIS0
U$5: ACTIVE1
U$6: #3V3#0
U$7: ANTENNA2
U$8: EC10
U$9: L1#L20
U$10: #PPS#1
U$13: SW0
U$14, U$17: FACET2
U$15, U$19: RTK0
U$16, U$18: SURVEYOR1
U$20: 140
U$21: 321
U$22: 332
U$23: I353
U$24: STAT0
U$25: #I�C#0
U$26: ##ERST##0
U$30: QWIIC_4MM
U$84: #GND#1

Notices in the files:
parts and their libraries:
SparkFun-Aesthetics: Licensing: Creative Commons ShareAlike 4.0 International - https://creativecommons.org/licenses/by-sa/4.0
SparkFun-Aesthetics: Released under the Creative Commons Attribution Share-Alike 4.0 License
SparkFun-Aesthetics: https://creativecommons.org/licenses/by-sa/4.0
